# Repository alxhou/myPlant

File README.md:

myPlant
=======

ESP8266 based soil moisture sensor WiFi enabled. Uses capacitive sensing inspired by the [I2C Moisture Sensor](https://github.com/Miceuz/i2c-moisture-sensor) project from Miceuz. Thanks for his source code. 

Repository Contents
-------------------

* **/Firmware** - Arduino source code (.ino, .h)
* **/Hardware** - All Eagle design files (.brd, .sch)

License Information
-------------------

This design is [OSHW](http://www.oshwa.org/definition/) and public domain but you buy me a beer if you use this and we meet someday ([Beerware license](http://en.wikipedia.org/wiki/Beerware)).

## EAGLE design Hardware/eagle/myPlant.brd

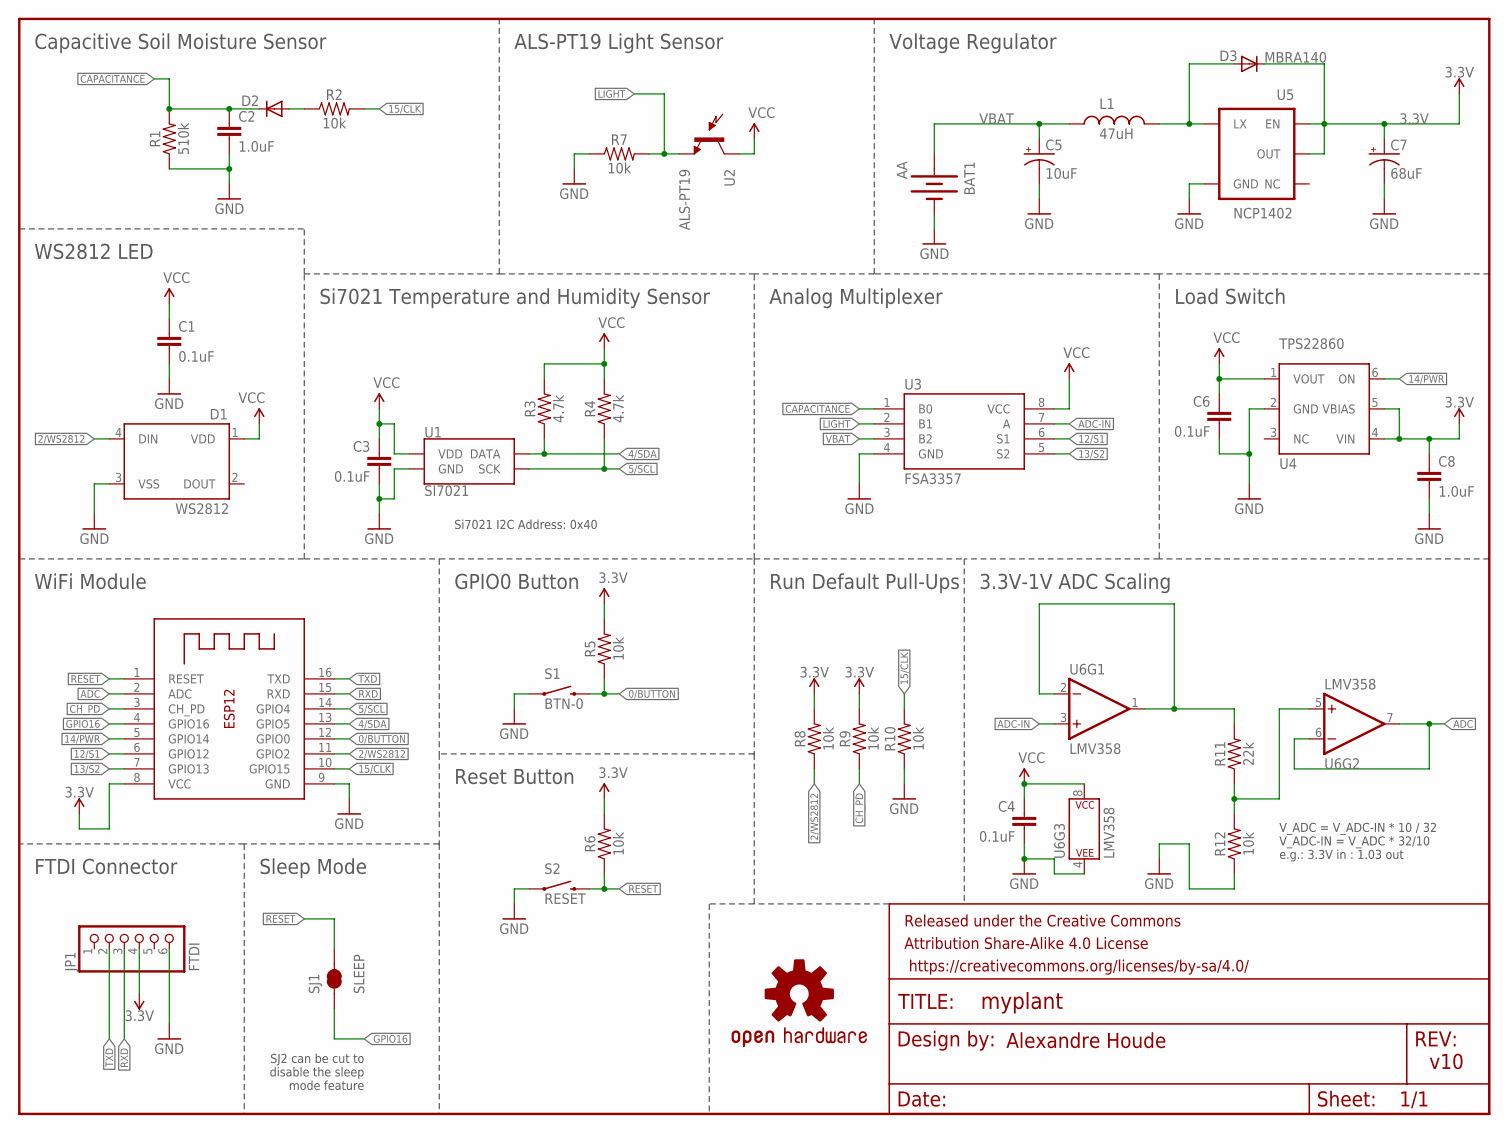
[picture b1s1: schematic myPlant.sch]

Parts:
BAT1: AA; BATTERY-AA-KIT
C1, C3, C4, C6: 0.1uF; 0603
C2, C8: 1.0uF; 0603
C5: 10uF; EIA3216
C7: 68uF; EIA3528
D1: WS2812; WS2812B
D2: DIODE-SCHOTTKY_; SOD-523
D3: MBRA140; SMA-DIODE
FRAME1: FRAME-LETTER; CREATIVE_COMMONS
JP1: FTDI; 1X06_ROUND_70
L1: 47uH; CR54
LOGO2: OSHW-LOGOS; OSHW-LOGO-S
R1: 510k; 0603
R2, R5, R6, R7, R8, R9, R10, R12: 10k; 0603
R3, R4: 4.7k; 0603
R11: 22k; 0603
S1: BTN-0; TACTILE_SWITCH_SMD_4.6X2.8MM
S2: RESET; TACTILE_SWITCH_SMD_4.6X2.8MM
SJ1: SLEEP; PAD-JUMPER-2-NC_BY_TRACE_YES_SILK
U1: SI7021; DFN-6-3X3-SI7021
U2: ALS-PT19
U3: FSA3357; US8
U4: TPS22860; SOT23-6
U5: NCP1402; SOT23-5
U6: LMV358; MSOP8
X1: ESP-12

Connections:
0/BUTTON: R5.1, S1.3 (2), S1.4 (2), X1.12 (GPIO0)
2/WS2812: D1.4 (DIN), R8.1, X1.11 (GPIO2)
3.3V: C7.A (+), C8.1, D3.C, JP1.4, R5.2, R6.2, R8.2, R9.2, U4.4 (VIN), U4.5 (VBIAS), U5.1 (EN), U5.2 (OUT), X1.8 (VCC)
4/SDA: R3.1, U1.DATA, X1.13 (GPIO5)
5/SCL: R4.1, U1.SCK, X1.14 (GPIO4)
12/S1: U3.6 (S1), X1.6 (GPIO12)
13/S2: U3.5 (S2), X1.7 (GPIO13)
14/PWR: U4.6 (ON), X1.5 (GPIO14)
15/CLK: R2.2, R10.2, X1.10 (GPIO15)
ADC: U6.6 (-IN), U6.7 (OUT), X1.2 (ADC)
ADC-IN: U3.7 (A), U6.3 (+IN)
CAPACITANCE: C2.1, D2.K (C), R1.2, U3.1 (B0)
CH_PD: R9.1, X1.3 (CH_PD)
GND: BAT1.GND@1 (-), C1.2, C2.2, C3.2, C4.2, C5.C (-), C6.2, C7.C (-), C8.2, D1.3 (VSS), JP1.6, R1.1, R7.1, R10.1, R12.1, S1.1, S1.2 (1), S2.1, S2.2 (1), U1.GND, U3.4 (GND), U4.2 (GND), U5.4 (GND), U6.4 (P$V-), X1.9 (GND)
GPIO16: SJ1.1, X1.4 (GPIO16)
LIGHT: R7.2, U2.E (E1), U3.2 (B1)
unnamed: D3.A, L1.P$2 (2), U5.5 (LX)
unnamed: R11.2, U6.1 (OUT), U6.2 (-IN)
unnamed: R11.1, R12.2, U6.5 (+IN)
RESET: R6.1, S2.3 (2), S2.4 (2), SJ1.2, X1.1 (RESET)
RXD: JP1.3, X1.15 (RXD)
TXD: JP1.2, X1.16 (TXD)
VBAT: BAT1.PWR@1 (+), C5.A (+), L1.P$1 (1), U3.3 (B2)
VCC: C1.1, C3.1, C4.1, C6.1, D1.1 (VDD), R3.2, R4.2, U1.VDD, U2.C (C1), U3.8 (VCC), U4.1 (VOUT), U6.8 (P$V+)
V_CAP: D2.A, R2.1

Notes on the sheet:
Si7021 I2C Address: 0x40
V_ADC = V_ADC-IN * 10 / 32 V_ADC-IN = V_ADC * 32/10 e.g.: 3.3V in : 1.03 out
Alexandre Houde
v10
Capacitive Soil Moisture Sensor
Voltage Regulator
Load Switch
3.3V-1V ADC Scaling
WiFi Module
WS2812 LED
ALS-PT19 Light Sensor
Analog Multiplexer
Si7021 Temperature and Humidity Sensor
GPIO0 Button
FTDI Connector
Run Default Pull-Ups
Sleep Mode
Reset Button
SJ2 can be cut to disable the sleep mode feature

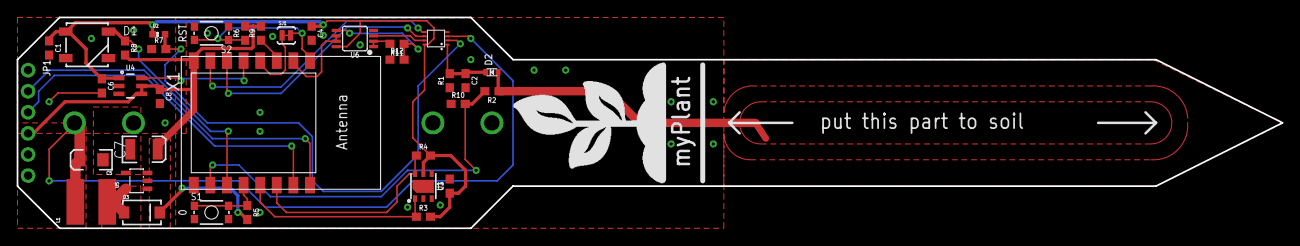
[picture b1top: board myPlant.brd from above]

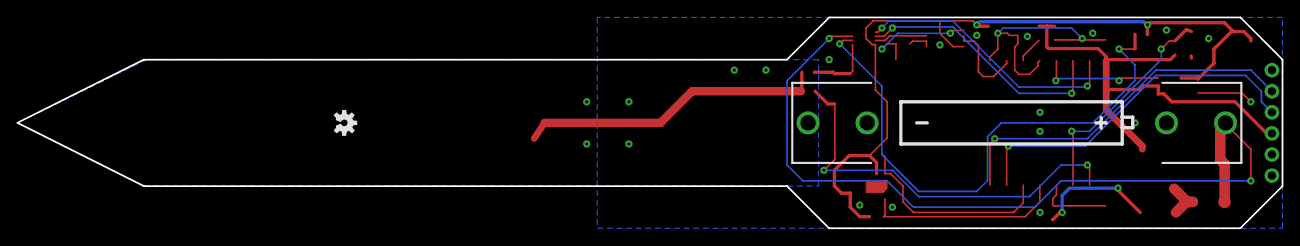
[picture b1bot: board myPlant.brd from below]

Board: 2 copper layers, 152.4 x 25.4 mm, 38 parts (2 on the bottom side), 25 nets.

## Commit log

2017-06-10 Initial Commit
    Initial firmware, based on Blynk demo app.
    http://www.blynk.io/demo/
2017-06-11 Added load switch
2017-06-11 Added project description
2017-06-15 Done preliminary pcb placement
2017-06-16 Complete PCB layout
2017-06-23 Change file location
2017-06-23 Corrected DRC errors
2017-06-23 Added datasheets
2017-07-11 Implemented analog and digital sensors
2017-07-19 Implemented RGB led and soil moisture sensor calibration
2017-08-05 Added Twitter notification
2017-08-13 Final version (for demo)
2017-10-02 Added getting started guide

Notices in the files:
parts and their libraries:
SparkFun-Capacitors: Licensing: Creative Commons ShareAlike 4.0 International - https://creativecommons.org/licenses/by-sa/4.0
SparkFun-Aesthetics: Released under the Creative Commons Attribution Share-Alike 4.0 License
SparkFun-Aesthetics: https://creativecommons.org/licenses/by-sa/4.0
